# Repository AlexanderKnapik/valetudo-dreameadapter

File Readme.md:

# Dreame Breakout

An improved version, of the original Dreame breakout adapter, relaid out with signal integrity in mind. Supports both UART and Fastboot methods. Refer to [valetudo-dreameadapter](https://github.com/Hypfer/valetudo-dreameadapter) for build instructions.

# Fastboot Breakout

A Fastboot only capable breakout board using a USB-C connector.

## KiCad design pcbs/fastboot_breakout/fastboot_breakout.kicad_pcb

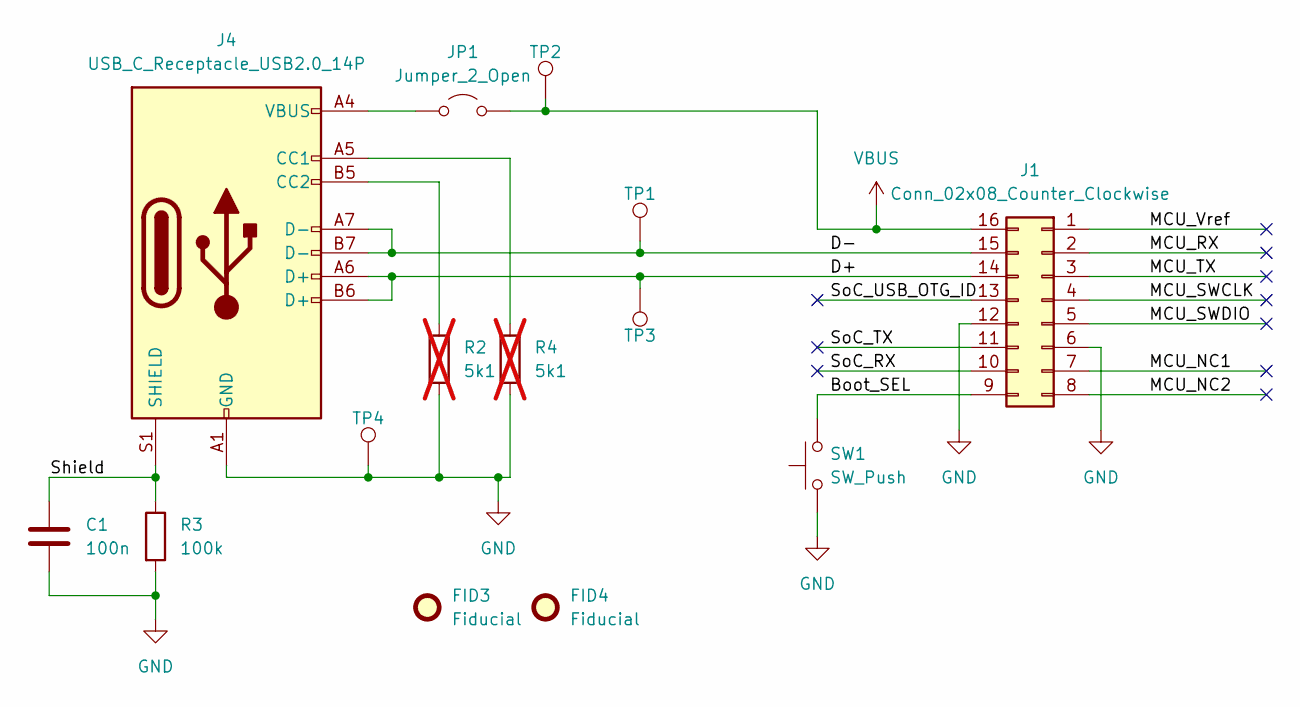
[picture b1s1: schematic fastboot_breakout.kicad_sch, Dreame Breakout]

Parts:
C1: 100n; C_0603_1608Metric_Pad1.08x0.95mm_HandSolder
FID3, FID4: Fiducial; Fiducial_1mm_Mask2mm
J1: Conn_02x08_Counter_Clockwise; Connector 02x08 2.00mm Edge Mount
J4: USB_C_Receptacle_USB2.0_14P; USB_C_Receptacle_GCT_USB4110
JP1: Jumper_2_Open; SolderJumper-2_P1.3mm_Open_TrianglePad1.0x1.5mm
R2, R4: 5k1; R_0603_1608Metric_Pad0.98x0.95mm_HandSolder; not fitted
R3: 100k; R_0603_1608Metric_Pad0.98x0.95mm_HandSolder
SW1: SW_Push; SW_Push_SPST_NO_Alps_SKRP
TP1, TP2, TP3, TP4: TestPoint; TestPoint_Pad_D1.5mm

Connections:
/Boot_SEL: J1.9, SW1.2
/D+: J1.14, J4.A6 (D+), J4.B6 (D+), TP3.1
/D-: J1.15, J4.A7 (D-), J4.B7 (D-), TP1.1
/MCU_NC1: J1.7
/MCU_NC2: J1.8
/MCU_RX: J1.2
/MCU_SWCLK: J1.4
/MCU_SWDIO: J1.5
/MCU_TX: J1.3
/MCU_Vref: J1.1
/Shield: C1.1, J4.S1 (SHIELD), R3.1
/SoC_RX: J1.10
/SoC_TX: J1.11
/SoC_USB_OTG_ID: J1.13
GND: C1.2, J1.6, J1.12, J4.A1 (GND), J4.A12 (GND), J4.B1 (GND), J4.B12 (GND), R2.2, R3.2, R4.2, SW1.1, TP4.1
unnamed: J4.A5 (CC1), R4.1
unnamed: J4.B5 (CC2), R2.1
unnamed: J4.A4 (VBUS), J4.A9 (VBUS), J4.B4 (VBUS), J4.B9 (VBUS), JP1.1 (A)
VBUS: J1.16, JP1.2 (B), TP2.1

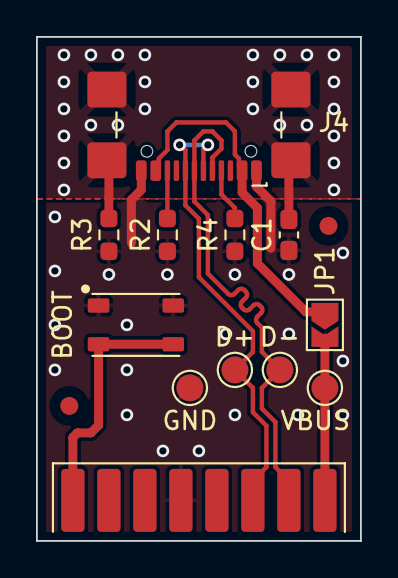
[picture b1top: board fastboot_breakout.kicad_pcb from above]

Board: 2 copper layers, 18.0 x 28.0 mm, 14 parts (1 on the bottom side), 9 nets.

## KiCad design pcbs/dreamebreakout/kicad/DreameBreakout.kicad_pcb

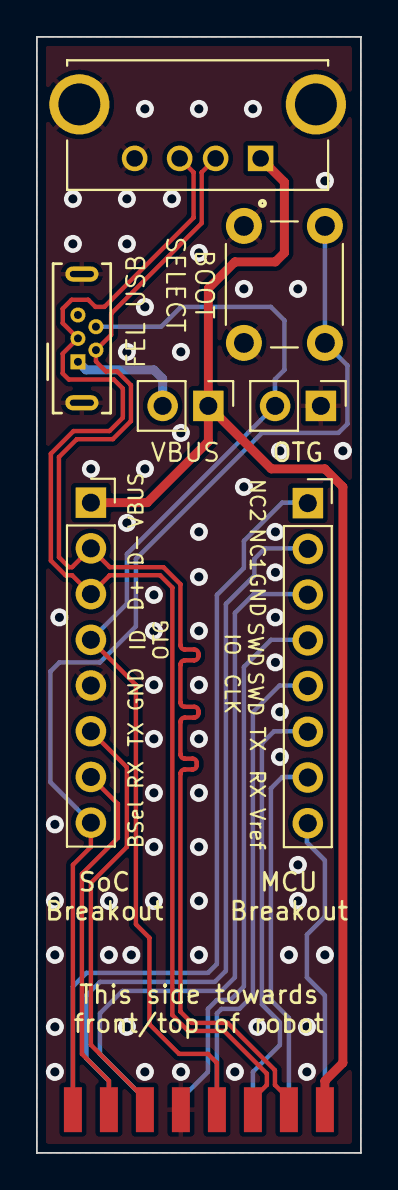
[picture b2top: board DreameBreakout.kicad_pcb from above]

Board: 2 copper layers, 18.0 x 62.0 mm, 9 parts (1 on the bottom side), 17 nets.

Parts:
J1: OTG_USB; ONSHORE_USB-A1VSB6
J1.1: To Robot SoC; DGI_8_SMDPADS
J1.2: To Robot MCU; DGI_8_SMDPADS
J2: SoC_FEL_USB; USB_Micro-B_Wuerth_614105150721_Vertical
J4: MCU Breakout; PinSocket_1x08_P2.54mm_Vertical
J5: SoC Breakout; PinSocket_1x08_P2.54mm_Vertical
JP1: JP_USB_VBUS; PinHeader_1x02_P2.54mm_Vertical
JP2: JP_USB_OTG_ID; PinHeader_1x02_P2.54mm_Vertical
SW1: SoC_Boot_SEL_BTN; SW_PUSH_6mm

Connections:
/Boot_SEL: J1.1.1, J5.8, SW1.2
/D+: J1.3 (D+), J1.1.6, J2.3 (D+), J5.3
/D-: J1.2 (D-), J1.1.7, J2.2 (D-), J5.2
/MCU_GND: J1.2.6, J4.3
/MCU_NC1: J1.2.7, J4.2
/MCU_NC2: J1.2.8, J4.1
/MCU_RX: J1.2.2, J4.7
/MCU_SWCLK: J1.2.4, J4.5
/MCU_SWDIO: J1.2.5, J4.4
/MCU_TX: J1.2.3, J4.6
/MCU_Vref: J1.2.1, J4.8
/SoC_RX: J1.1.2, J5.7
/SoC_TX: J1.1.3, J5.6
/SoC_USB_OTG_ID: J1.1.5, J2.4 (ID), J5.4, JP2.2 (B)
/USB_VBUS: J2.1 (VBUS), JP1.2 (B)
/VBUS: J1.1 (VBUS), J1.1.8, J5.1, JP1.1 (A)
GND: J1.4 (GND), J1.5 (Shield), J1.1.4, J2.5 (GND), J2.6 (Shield), J5.5, JP2.1 (A), SW1.1

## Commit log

2025-12-10 Kicad .gitignore
2025-12-10 Update original Dreame breakout board
2025-12-10 Fastboot only USB-C breakout board
2025-12-10 Readme refers to project differences
2025-12-30 Add fastboot breakout image to readme.md
